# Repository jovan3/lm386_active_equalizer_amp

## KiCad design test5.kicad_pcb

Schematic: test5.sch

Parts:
10K1: 10K; R_Axial_DIN0204_L3.6mm_D1.6mm_P7.62mm_Horizontal
C1, C2: 100uF; CP_Radial_D5.0mm_P2.50mm
C3, C4, C5, C6, C11, C12, C13, C14, C15, C16, C17, C18, C23, C24, C25, C26: 3.3nF; C_Disc_D3.4mm_W2.1mm_P2.50mm
C7, C8, C9, C10, C19, C20, C21, C22, C35, C36: 47nF; C_Disc_D3.4mm_W2.1mm_P2.50mm
C27, C28, C29, C30, C31, C32, C33, C34: 33nF; C_Disc_D3.4mm_W2.1mm_P2.50mm
C37, C38: 1000uF; CP_Radial_D10.0mm_P5.00mm
J1, J2: JACK_TRS; Tayda_3.5mm_stereo_TRS_jack_A-853
J3: Conn_01x04_Female; PinHeader_1x04_P2.54mm_Vertical
R1, R2, R3, R4, R5, R6, R7, R8, R9, R10, R11, R12, R25, R26, R27, R28, R29, R30, R31, R32, R33, R34, R35, R36, R55, R56, R57, R58, R66, R67, R68, R69: 47K; R_Axial_DIN0204_L3.6mm_D1.6mm_P7.62mm_Horizontal
R13, R15, R17, R19, R21, R23, R59, R61: 1.5K; R_Axial_DIN0204_L3.6mm_D1.6mm_P7.62mm_Horizontal
R14, R16, R18, R20, R22, R24, R38, R39, R41, R42, R44, R45, R47, R48, R50, R51, R53, R54, R60, R62, R63, R64, R65, R70, R74, R75, R77, R78: 10K; R_Axial_DIN0204_L3.6mm_D1.6mm_P7.62mm_Horizontal
R37, R40, R43, R46, R49, R52, R73, R76: 2.2K; R_Axial_DIN0204_L3.6mm_D1.6mm_P7.62mm_Horizontal
R71: R; R_Axial_DIN0204_L3.6mm_D1.6mm_P7.62mm_Horizontal
R79, R80: 10; R_Axial_DIN0204_L3.6mm_D1.6mm_P7.62mm_Horizontal
RV1, RV2, RV3, RV4: 10K; Potentiometer_Alps_RK097_Dual_Horizontal
U1, U2, U3, U4, U5, U6, U7, U8: NE5532; DIP-8_W7.62mm
U9, U10: LM386; DIP-8_W7.62mm

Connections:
GND: C1.2, C2.1, C7.2, C8.2, C11.2, C12.2, C19.1, C20.1, C23.1, C24.1, C35.2, C36.2, J1.1, J2.1, J3.2, J3.3, R9.1, R10.1, R14.1, R16.1, R18.1, R20.1, R22.1, R24.1, R33.1, R34.1, R39.2, R42.2, R45.2, R48.2, R51.2, R54.2, R55.1, R56.1, R60.1, R62.1, R66.1, R67.1, R75.2, R78.2, RV1.1, RV1.4, RV2.1, RV2.4, RV3.1, RV3.4, RV4.1, RV4.4, U9.2, U9.4, U10.2, U10.4
IN_LEFT: C4.2, J1.3, R2.1, R4.1
IN_RIGHT: C3.2, J1.2, R1.1, R3.1
unnamed: 10K1.1, R70.1, R71.1, RV3.3
unnamed: 10K1.2, RV4.2
unnamed: C3.1, C5.2, R11.2
unnamed: C4.1, C6.2, R12.2
unnamed: C5.1, R9.2, U3.3 (+)
unnamed: C6.1, R10.2, U4.3 (+)
unnamed: C7.1, R5.1, U1.3 (+)
unnamed: C8.1, R6.1, U2.3 (+)
unnamed: C9.1, R13.1, R25.1, U1.1
unnamed: C9.2, R1.2, R5.2
unnamed: C10.1, R15.1, R26.1, U2.1
unnamed: C10.2, R2.2, R6.2
unnamed: C11.1, R7.1, U5.3 (+)
unnamed: C12.1, R8.1, U6.3 (+)
unnamed: C13.1, R21.1, R27.1, U5.1
unnamed: C13.2, R3.2, R7.2
unnamed: C14.1, R23.1, R28.1, U6.1
unnamed: C14.2, R4.2, R8.2
unnamed: C15.1, C17.2, R35.2
unnamed: C15.2, R11.1, R17.1, U3.1
unnamed: C16.1, C18.2, R36.2
unnamed: C16.2, R12.1, R19.1, U4.1
unnamed: C17.1, R33.2, U3.5 (+)
unnamed: C18.1, R34.2, U4.5 (+)
unnamed: C19.2, R29.2, U1.5 (+)
unnamed: C20.2, R30.2, U2.5 (+)
unnamed: C21.1, R37.1, RV1.6, U1.7
unnamed: C21.2, R25.2, R29.1
unnamed: C22.1, R40.1, RV1.3, U2.7
unnamed: C22.2, R26.2, R30.1
unnamed: C23.2, R31.2, U5.5 (+)
unnamed: C24.2, R32.2, U6.5 (+)
unnamed: C25.1, C27.2, R49.1, U5.7
unnamed: C25.2, R27.2, R31.1
unnamed: C26.1, C28.2, R52.1, U6.7
unnamed: C26.2, R28.2, R32.1
unnamed: C27.1, C29.2, R57.2
unnamed: C28.1, C30.2, R58.2
unnamed: C29.1, R55.2, U7.3 (+)
unnamed: C30.1, R56.2, U8.3 (+)
unnamed: C31.1, C33.2, R68.2
unnamed: C31.2, R57.1, R59.1, U7.1
unnamed: C32.1, C34.2, R69.2
unnamed: C32.2, R58.1, R61.1, U8.1
unnamed: C33.1, R66.2, U7.5 (+)
unnamed: C34.1, R67.2, U8.5 (+)
unnamed: C35.1, R79.2
unnamed: C36.1, R80.2
unnamed: C37.1, R79.1, U9.5
unnamed: C37.2, J2.2
unnamed: C38.1, R80.1, U10.5
unnamed: C38.2, J2.3
unnamed: R13.2, R14.2, U1.2 (-)
unnamed: R15.2, R16.2, U2.2 (-)
unnamed: R17.2, R18.2, U3.2 (-)
unnamed: R19.2, R20.2, U4.2 (-)
unnamed: R21.2, R22.2, U5.2 (-)
unnamed: R23.2, R24.2, U6.2 (-)
unnamed: R35.1, R43.1, RV2.6, U3.7
unnamed: R36.1, R46.1, RV2.3, U4.7
unnamed: R37.2, R38.1
unnamed: R38.2, R39.1, U1.6 (-)
unnamed: R40.2, R41.1
unnamed: R41.2, R42.1, U2.6 (-)
unnamed: R43.2, R44.1
unnamed: R44.2, R45.1, U3.6 (-)
unnamed: R46.2, R47.1
unnamed: R47.2, R48.1, U4.6 (-)
unnamed: R49.2, R50.1
unnamed: R50.2, R51.1, U5.6 (-)
unnamed: R52.2, R53.1
unnamed: R53.2, R54.1, U6.6 (-)
unnamed: R59.2, R60.2, U7.2 (-)
unnamed: R61.2, R62.2, U8.2 (-)
unnamed: R63.1, R64.1, R65.1, RV3.6
unnamed: R63.2, RV1.5
unnamed: R64.2, RV2.5
unnamed: R65.2, RV4.5
unnamed: R68.1, R73.1, RV4.6, U7.7
unnamed: R69.1, R76.1, RV4.3, U8.7
unnamed: R70.2, RV1.2
unnamed: R71.2, RV2.2
unnamed: R73.2, R74.1
unnamed: R74.2, R75.1, U7.6 (-)
unnamed: R76.2, R77.1
unnamed: R77.2, R78.1, U8.6 (-)
unnamed: RV3.2, U10.3
unnamed: RV3.5, U9.3
Vcc+: C1.1, J3.1, U1.8 (V+), U2.8 (V+), U3.8 (V+), U4.8 (V+), U5.8 (V+), U6.8 (V+), U7.8 (V+), U8.8 (V+), U9.6, U10.6
Vcc-: C2.2, J3.4, U1.4 (V-), U2.4 (V-), U3.4 (V-), U4.4 (V-), U5.4 (V-), U6.4 (V-), U7.4 (V-), U8.4 (V-)

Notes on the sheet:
Lowpass filter (right)
Highpass filter (right)
Bandpass filter (right)
Lowpass filter (left)
Highpass filter (left)
Bandpass filter (left)

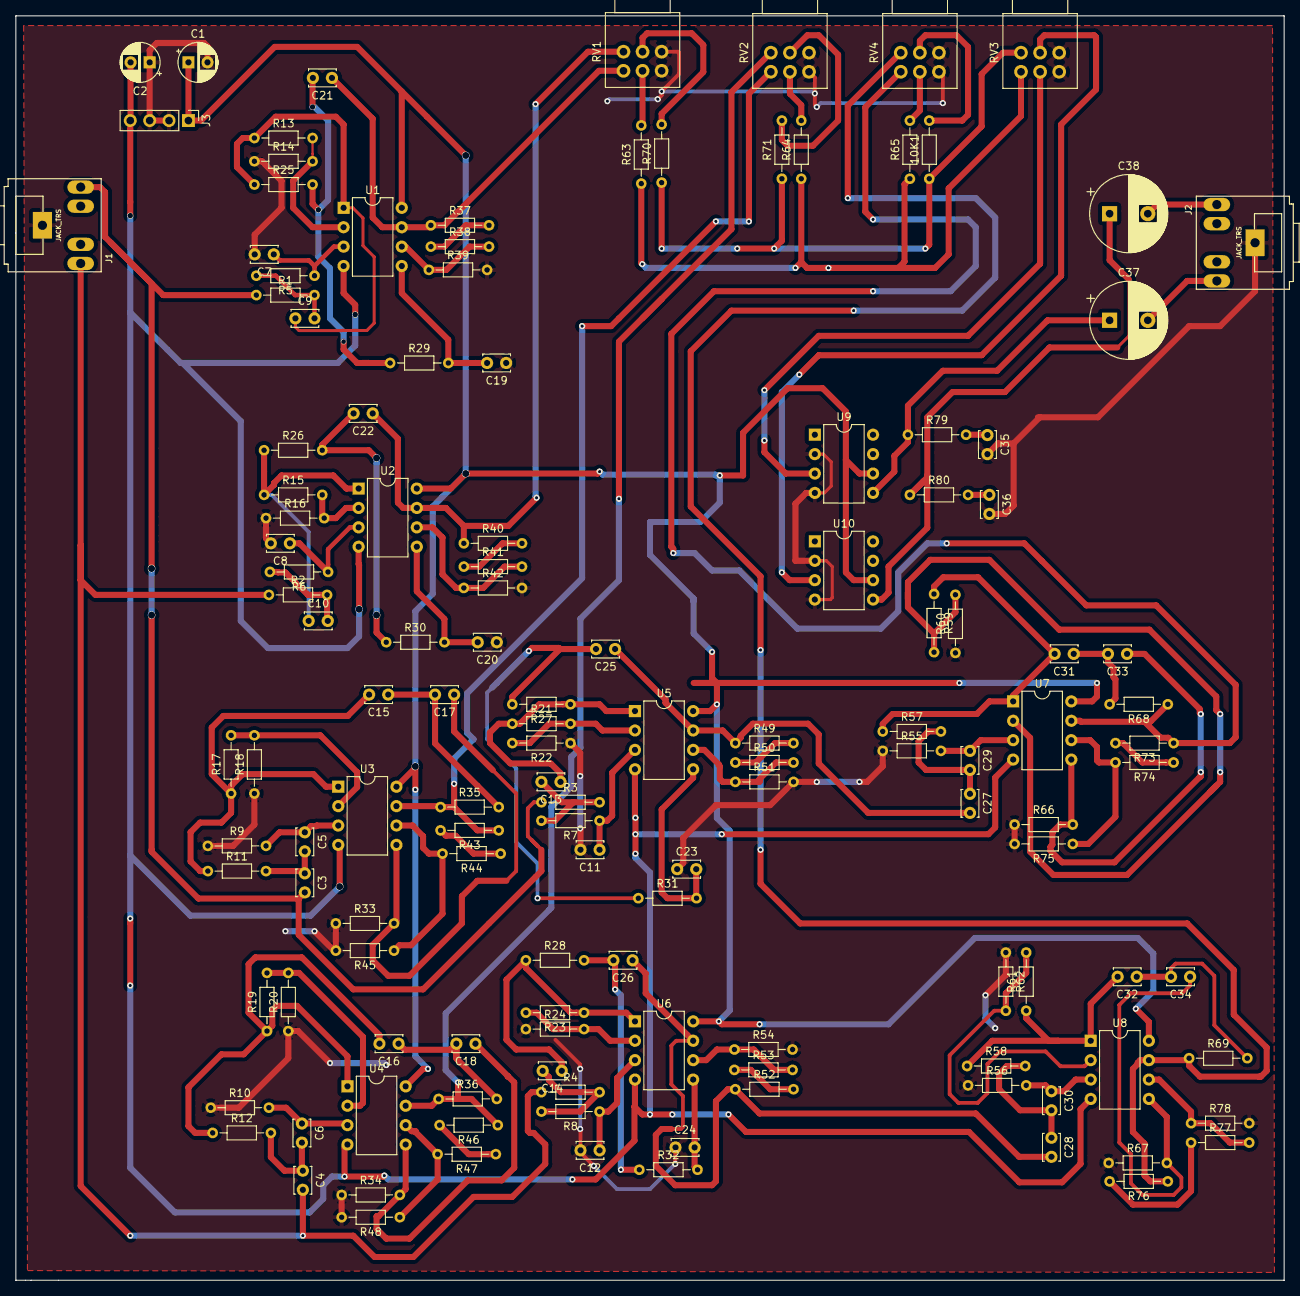
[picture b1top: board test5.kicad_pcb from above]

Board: 2 copper layers, 166.1 x 165.6 mm, 135 parts (0 on the bottom side), 93 nets.

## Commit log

2018-07-17 start arranging components on the PCB
2018-07-17 arrange some more components
2018-07-19 finalize layout
2018-07-20 optimize layout
